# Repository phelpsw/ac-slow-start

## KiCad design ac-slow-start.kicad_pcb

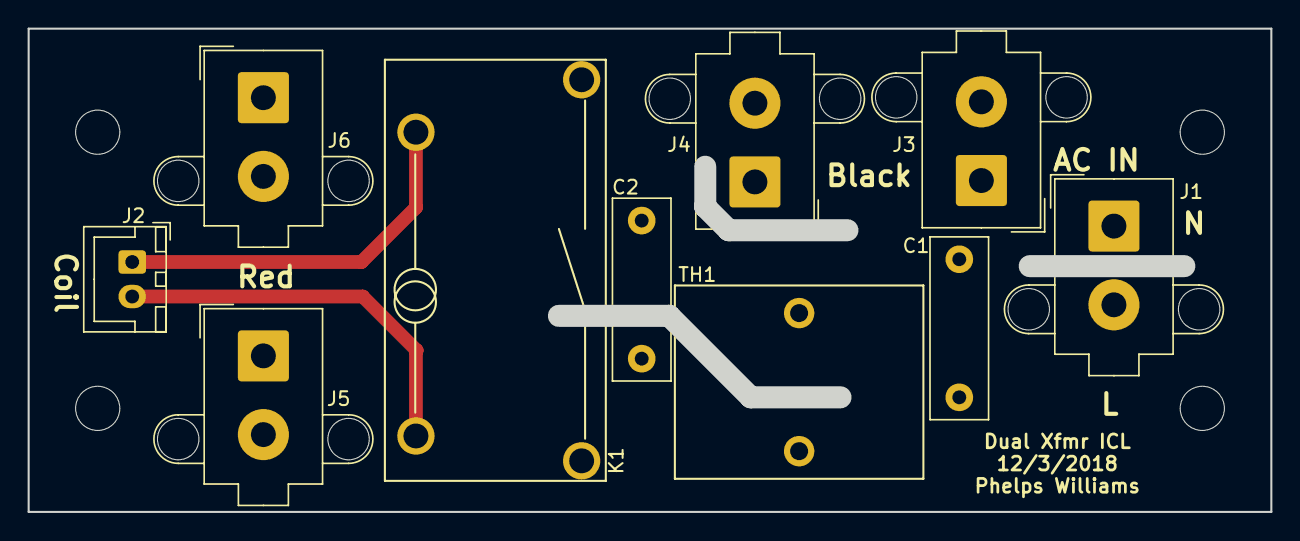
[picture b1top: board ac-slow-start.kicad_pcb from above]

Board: 2 copper layers, 88.5 x 33.6 mm, 14 parts (0 on the bottom side), 5 nets.

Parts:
C1, C2: 0.01uF/400V; C_Rect_L13.0mm_W4.0mm_P10.00mm_FKS3_FKP3_MKS4
H1, H2, H3, H4: MountingHole; MountingHole_3.2mm_M3_ISO14580
J1: Conn_01x02_Male; Molex_Mega-Fit_76829-0002_2x01_P5.70mm_Vertical
J2: Conn_01x02_Male; JST_XH_B02B-XH-A_1x02_P2.50mm_Vertical
J3, J4, J5, J6: Conn_01x02_Female; Molex_Mega-Fit_76829-0002_2x01_P5.70mm_Vertical
K1: G4A-1A-PE DC24; G4A-1A-PE
TH1: B59215J0130A020

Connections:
unnamed: C1.1, J1.1, J3.1, J3.2, J4.1, J4.2
unnamed: C1.2, C2.2, J1.2, K1.3, TH1.2
unnamed: C2.1, J5.1, J5.2, J6.1, J6.2, K1.2, TH1.1
unnamed: J2.1, K1.1
unnamed: J2.2, K1.5

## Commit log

2018-12-03 Adding initial ac-slow-start files
2018-12-04 Updating with new smaller footprint
2020-07-14 ac slow start tweaks from mfg
2020-07-14 Adding image
